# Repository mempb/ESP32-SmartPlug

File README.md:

# ESP32-C3 HomeKit Smart Plug

A standalone WiFi smart plug built around the ESP32-C3 Super Mini, exposing native Apple HomeKit control via [esp-homekit-sdk](https://github.com/espressif/esp-homekit-sdk).

## Overview

The ESP32-C3 connects directly to the home WiFi network and implements the HomeKit Accessory Protocol (HAP) on-device using Espressif's open-source `esp-homekit-sdk`. It advertises itself as a HomeKit accessory and pairs directly with the Apple Home app. A relay switches mains power to a connected load (tested with a small AC fan), with a local status LED and a manual push-button override.

## Hardware

- **MCU:** ESP32-C3 Super Mini (WiFi + BLE)
- **Relay:** Songle SRD-05VDC-SL-C
- **Relay drive:** 2N3904 NPN, low-side switched, 1k base resistor, 1N4007 flyback diode across the coil
- **Mains supply:** Hi-Link HLK-PM01 (AC → 5V)
- **I/O:** status LED, manual push-button (SW2)
- **Connectors:** 5.08mm pitch screw terminals for mains in/out
- Custom PCB (KiCad), hand-solderable THT components throughout

## Firmware

- **Toolchain:** PlatformIO, `framework = espidf`
- **Application logic:** plain ESP-IDF C — GPIO config, debounced button input, LED/relay control
- **HomeKit layer:** `esp-homekit-sdk` (Espressif's open-source HAP implementation), added as an ESP-IDF component
- WiFi credentials configured via `idf.py menuconfig` (hardcoded); HomeKit pairing done separately after WiFi connects via the HomeKit setup code

## Setup

- `git clone --recursive git@github.com:mempb/ESP32-SmartPlug.git`
- Install `PlatformIO` VSCode extension
- WiFi SSID & password: 
    - Option A: `pio run -t menuconfig` → App Wi-Fi → Source of Wi-Fi Credentials → Use Hardcoded → set SSID and password
    - Option B: edit `sdkconfig.esp32-c3-devkitm-1`:
      - `CONFIG_APP_WIFI_SSID="SSID"`
      - `CONFIG_APP_WIFI_PASSWORD="pass"`
- Build/flash: `pio run -t upload -t monitor`

## Roadmap

- [x] Schematic design
- [x] PCB layout and routing, order
- [x] PCB assembly (hand soldering)
- [X] GPIO firmware: button input, debounce, LED toggle
- [X] HomeKit firmware (esp-homekit-sdk integration, relay control, button + LED sync)
- [X] Respin PCB, order (smaller form factor, fix missing GND trace, add capacitor)
- [ ] Enclosure design/print
- [ ] Final writeup: build photos, schematics, wiring diagram, etc

## Repo Structure

```
/components esp-homekit-sdk location
/pcb        KiCad project
/src        ESP-IDF source
/docs       Schematics, pictures, etc. (TODO)
/housing    3D print housing design (TODO)
```

## References

- https://docs.espressif.com/projects/esp-idf/en/stable/esp32/index.html
- https://github.com/espressif/esp-homekit-sdk

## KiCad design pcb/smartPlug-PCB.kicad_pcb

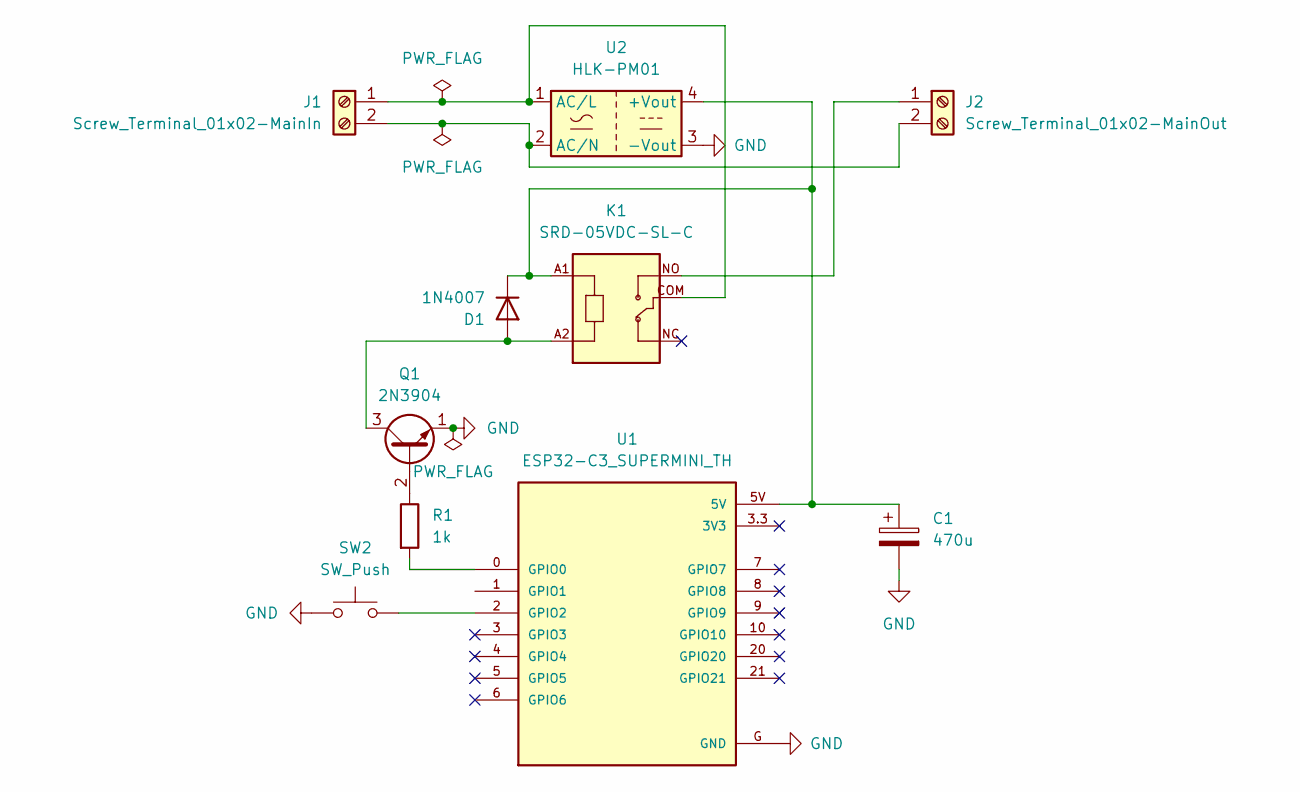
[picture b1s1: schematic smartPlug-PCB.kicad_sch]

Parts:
C1: 470u; CP_Radial_D8.0mm_P3.50mm
D1: 1N4007; D_DO-41_SOD81_P10.16mm_Horizontal
J1: Screw_Terminal_01x02-MainIn; TerminalBlock_Phoenix_MKDS-1,5-2-5.08_1x02_P5.08mm_Horizont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
J2: Screw_Terminal_01x02-MainOut; TerminalBlock_Phoenix_MKDS-1,5-2-5.08_1x02_P5.08mm_Horizont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
K1: SRD-05VDC-SL-C; RELAY_SRD-05VDC-SL-C
Q1: 2N3904; TO-92_Inline
R1: 1k; R_Axial_DIN0207_L6.3mm_D2.5mm_P10.16mm_Horizontal
SW2: SW_Push; SW_PUSH_6mm
U1: ESP32-C3_SUPERMINI_TH; MODULE_ESP32-C3_SUPERMINI_TH
U2: HLK-PM01; Converter_ACDC_Hi-Link_HLK-PMxx

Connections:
GND: C1.2, Q1.1 (E), SW2.1, U1.G (GND), U2.3 (-Vout)
unnamed: D1.2 (A), K1.A2, Q1.3 (C)
unnamed: C1.1, D1.1 (K), K1.A1, U1.5V, U2.4 (+Vout)
unnamed: J1.1, K1.COM, U2.1 (AC/L)
unnamed: J1.2, J2.2, U2.2 (AC/N)
unnamed: J2.1, K1.NO
unnamed: Q1.2 (B), R1.1
unnamed: R1.2, U1.0 (GPIO0)
unnamed: SW2.2, U1.2 (GPIO2)

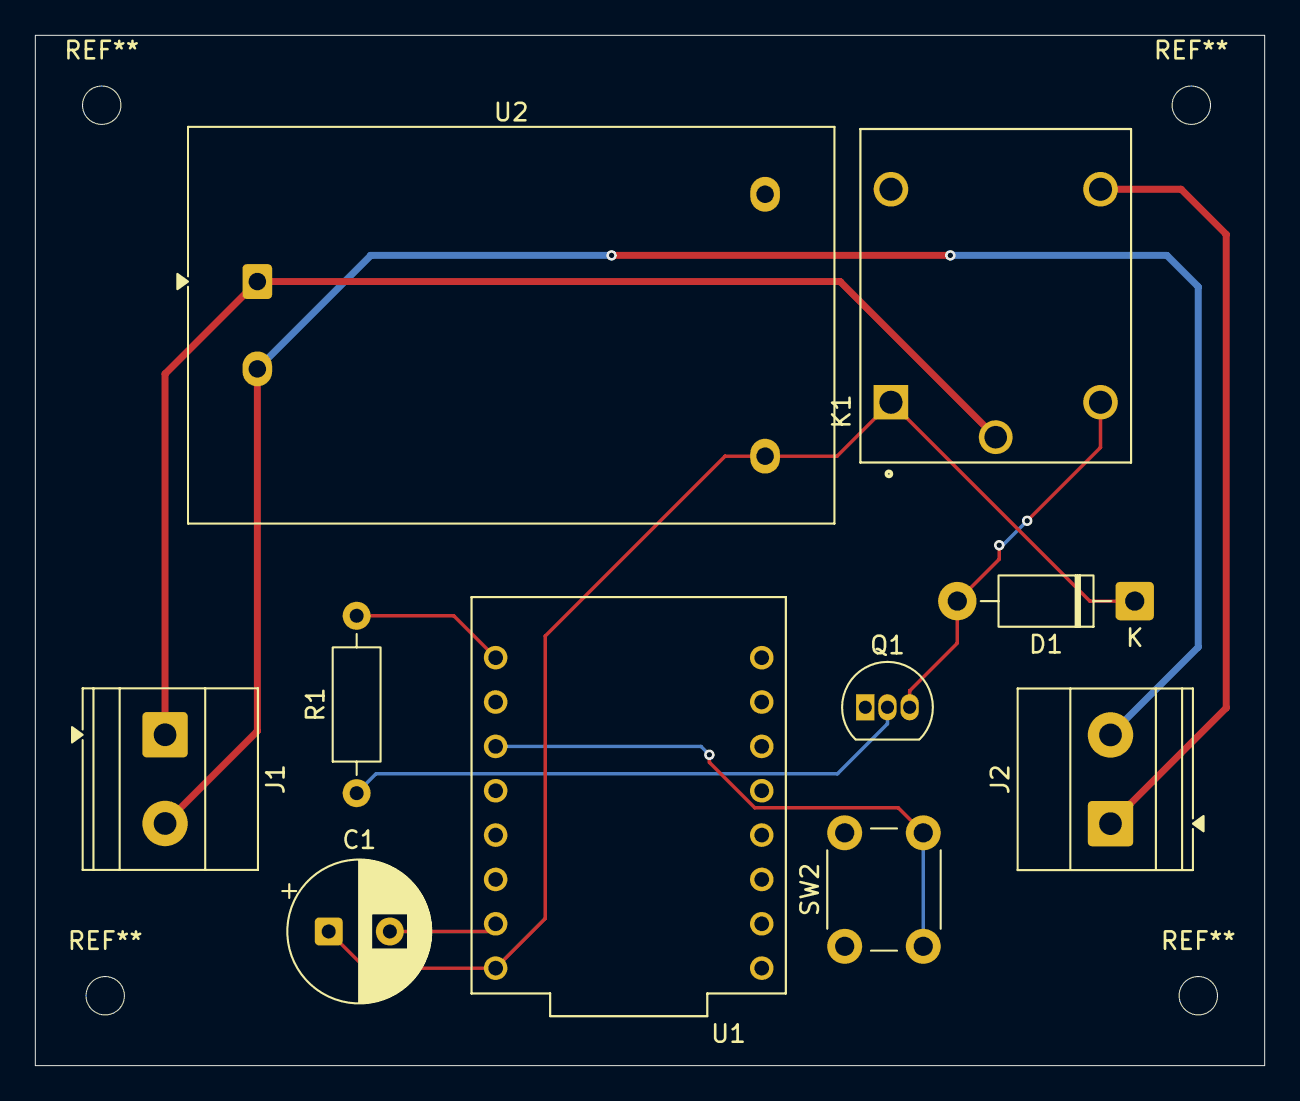
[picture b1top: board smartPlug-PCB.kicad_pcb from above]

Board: 2 copper layers, 70.4 x 59.0 mm, 10 parts (0 on the bottom side), 9 nets.
